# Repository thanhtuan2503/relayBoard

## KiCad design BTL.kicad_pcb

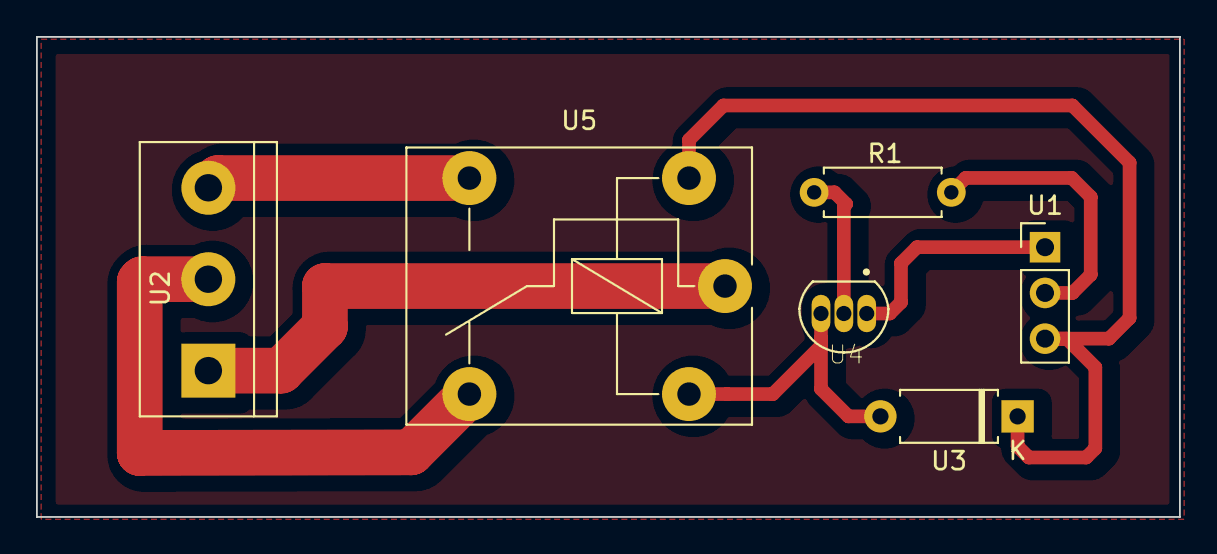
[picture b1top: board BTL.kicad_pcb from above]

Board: 2 copper layers, 63.5 x 26.7 mm, 6 parts (0 on the bottom side), 8 nets.

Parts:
R1: 1k; R_Axial_DIN0207_L6.3mm_D2.5mm_P7.62mm_Horizontal
U1: INPUT_BLOCK; PinHeader_1x03_P2.54mm_Vertical
U2: OUTPUT_BLOCK; TerminalBlock_bornier-3_P5.08mm
U3: DIODE; D_A-405_P7.62mm_Horizontal
U4: 2N3904
U5: YL303H; Relay_SPDT_Finder_36.11

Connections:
unnamed: R1.1, U4.2
unnamed: R1.2, U1.2
unnamed: U1.1, U4.1
unnamed: U1.3, U3.1, U5.A1
unnamed: U2.1, U5.11
unnamed: U2.2, U5.12
unnamed: U2.3, U5.14
unnamed: U3.2, U4.3, U5.A2

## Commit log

2021-07-04 Upload file first time
2021-07-04 Format folder
